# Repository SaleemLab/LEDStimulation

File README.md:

# Full-Field LED Visual Stimulator

An open-source, high-precision visual stimulation platform designed for visual neuroscience, sensory physiology, and human psychophysics. The system delivers temporally agile, multi-chromatic optical stimulation (e.g., Green for M-cones/rods and UV for S-cones, or custom multi-spectral arrays) with sub-millisecond precision.

https://github.com/user-attachments/assets/08af2269-a270-4899-ae75-62786a714254

*Example stimulus: 2 Hz antiphase (Green / UV) sinusoidal flicker.*

---

## Key Capabilities

- **High-Resolution Temporal Modulation:** 16-bit Phase-Correct carrier PWM (~7.68–10 kHz) combined with hardware-interrupt pacing (Timer3 CTC ISR) eliminates visible digital stepping and software loop jitter.
- **Rich Stimulus Battery:** Native microsecond-timed generation of sinusoidal flickers, Gaussian white noise (with Central Limit Theorem PRNG), contrast-switching adaptation sequences, exponential frequency chirps, and stepped luminance pulses.
- **Quantitative Radiometric Calibration:** End-to-end MATLAB calibration pipeline mapping raw duty cycles to linearized lookup tables (LUTs) and calculating exact photoreceptor isomerisation rates ($R^*/\text{photoreceptor/s}$).
- **Flexible Form Factors:** Supports both 200mm full-field panel enclosures (with magnetic diffusion clamping) and miniature wearable mounts for Pupil Labs Neon eye-tracking glasses.
- **Reactive Experiment Orchestration:** Full integration with [Bonsai](https://bonsai-rx.org/) for closed-loop, state-dependent, adaptive psychometric staircase, and LabStreamingLayer (LSL) multi-modal recording.

---

## System Architecture

```mermaid
graph LR
    subgraph Host Software
        Bonsai[Bonsai Reactive Workflows]
        LSL[LabStreamingLayer / LabRecorder]
        MATLAB[MATLAB Calibration Suite]
    end

    subgraph Microcontroller Firmware
        MCU[Arduino Leonardo / Teensy 4.1]
        T1[Timer1: 16-bit PWM]
        T3[Timer3: CTC Interrupt Pacing]
        LUT[PROGMEM Gamma LUT]
    end

    subgraph Hardware & Optics
        Driver[Multi-Channel Driver Stage]
        LEDs[Dual-Channel LED Arrays]
        Enclosure[Magnetic Diffusion Enclosure / Glasses]
        Sensors[Photodiode / Power Meter / Eye Tracker]
    end

    Bonsai -- Serial ASCII (115200) --> MCU
    MATLAB -. Offline Calibration .-> LUT
    MCU --> T1 & T3
    T3 --> LUT --> T1
    T1 --> Driver --> LEDs --> Enclosure
    Enclosure -. Optical Feedback .-> Sensors
    Sensors --> LSL
```

---

## Quickstart Guide

### 1. Flash the Firmware
1. Open [`ArduinoCode/StimulusControlViaSerial_Leonardo_v8/StimulusControlViaSerial_Leonardo_v8.ino`](file:///d:/Code/LEDStimulation/ArduinoCode/StimulusControlViaSerial_Leonardo_v8/StimulusControlViaSerial_Leonardo_v8.ino) in the Arduino IDE.
2. Select **Arduino Leonardo** as your board and choose the corresponding COM port.
3. Click **Upload**.

### 2. Connect Hardware & Verify
1. Connect your LED driver to the designated MCU pins (PWM: Pins 9 & 10; Indicators: Pins 4 & 5).
2. Open the Serial Monitor at `115200` baud.
3. Send a test sinusoidal flicker:
   ```text
   s, 3000, 2.0, 0.0, 0.5, 0.8, 0.8
   ```
   *(Runs a 3-second, 2 Hz antiphase flicker on Channels A and B at 80% contrast).*

### 3. Launch Experimental Workflows
Open [Bonsai](https://bonsai-rx.org/) and load one of the pre-built visual stimulation workflows from [`BonsaiCode/`](file:///d:/Code/LEDStimulation/BonsaiCode/) (e.g., `LEDstimulation_normal.bonsai` or `ManualMethodOfAdjustment.bonsai`).

---

## Documentation Index

Comprehensive guides, schematics, and technical specifications are available in the **[`docs/`](docs/index.md)** directory:

| Section | Description |
| :--- | :--- |
| **[1. Hardware](docs/1-hardware/circuit-and-driver.md)** | [Circuit & Driver](docs/1-hardware/circuit-and-driver.md) • [Custom PCBs](docs/1-hardware/custom-pcbs.md) • [Panel Enclosure](docs/1-hardware/enclosure-and-optics/panel-enclosure.md) • [Wearable Glasses](docs/1-hardware/enclosure-and-optics/wearable-glasses.md) • [Bill of Materials](docs/1-hardware/bill-of-materials.md) |
| **[2. Firmware](docs/2-firmware/architecture-and-timers.md)** | [Architecture & Hardware Timers](docs/2-firmware/architecture-and-timers.md) • [Serial API Reference](docs/2-firmware/serial-api-reference.md) • [Firmware Variants](docs/2-firmware/firmware-variants.md) |
| **[3. Calibration](docs/3-calibration/calibration-guide.md)** | [Calibration Guide](docs/3-calibration/calibration-guide.md) • [Gamma LUT Pipeline](docs/3-calibration/gamma-lut-pipeline.md) • [Photoreceptor Calculations](docs/3-calibration/photoreceptor-calculations.md) |
| **[4. Experimental Workflows](docs/4-experimental-workflows/bonsai-overview.md)** | [Bonsai Setup](docs/4-experimental-workflows/bonsai-overview.md) • [Stimulation Paradigms](docs/4-experimental-workflows/stimulation-paradigms.md) • [Integration & Multi-Modal Sync](docs/4-experimental-workflows/integration-and-sync.md) |
| **[5. Reference](docs/5-reference/performance-and-sync.md)** | [Performance Characteristics, Switching Dynamics & Thermal Notes](docs/5-reference/performance-and-sync.md) |

---

## Repository Structure

```text
├── ArduinoCode/                  # Microcontroller firmware (Leonardo v8, DDS, Teensy 4.1, IMU)
├── BonsaiCode/                   # Main Bonsai visual reactive workflows & stimulus CSVs
├── BonsaiForHumanExperiments/    # Dedicated human psychophysics Bonsai workflows
├── Calibration/                  # MATLAB scripts for radiometry, gamma LUTs & opsin calculations
├── Hardware/                     # CAD files (.stp, .stl, .ipt), KiCad PCB designs & driver schematics
│   ├── Enclosure/                # Baseplate CAD & 3D printed magnetic diffusion clamps
│   ├── glasses/                  # Pupil Labs Neon glasses boom arm & miniature diffuser
│   ├── LED_board/                # KiCad dual-channel LED array PCB
│   └── LED_board_humans/         # KiCad 3-colour LED array PCB (WIP redesign with layout improvements)
├── HumanExpAnalysis/             # MATLAB scripts for IMU movement and behavioural analysis
├── LabRecorderFiles/             # Multi-modal LabStreamingLayer (LSL) recording configurations
└── docs/                         # Modular technical documentation
```

---

## License & Attribution

Developed for scientific research applications. If you use this platform in your research, please cite this repository.

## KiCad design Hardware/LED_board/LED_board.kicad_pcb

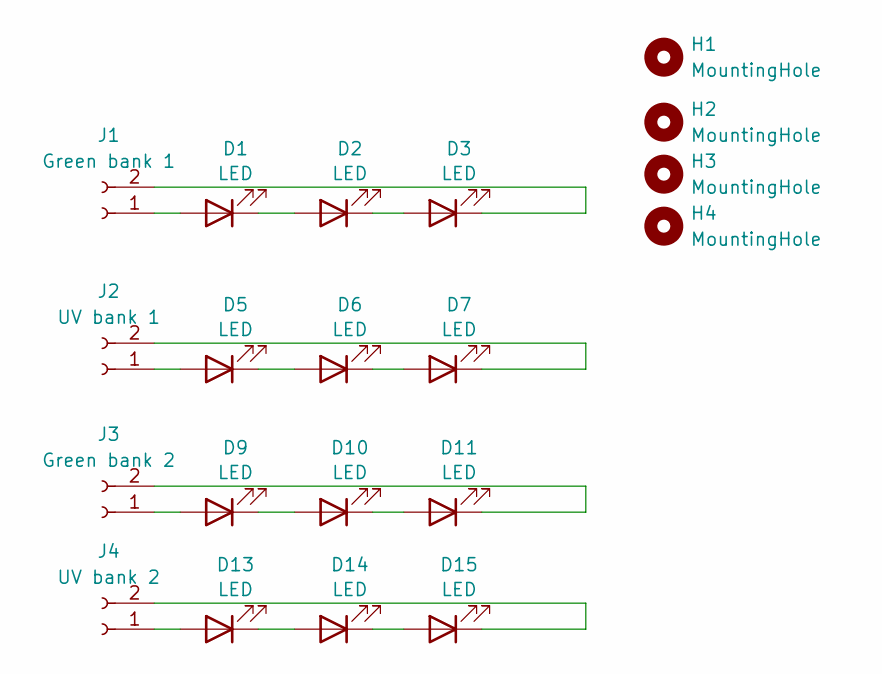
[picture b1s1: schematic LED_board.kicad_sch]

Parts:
D1, D2, D3, D9, D10, D11: LED; LED-SMD_L3.5-W2.8_RED
D5, D6, D7, D13, D14, D15: LED; LED-SMD_L3.5-W2.8-FD_WHITE-1
H1, H2, H3, H4: MountingHole; MountingHole_3.2mm_M3
J1: Green bank 1; PinSocket_1x02_P2.54mm_Horizontal
J2: UV bank 1; PinSocket_1x02_P2.54mm_Horizontal
J3: Green bank 2; PinSocket_1x02_P2.54mm_Horizontal
J4: UV bank 2; PinSocket_1x02_P2.54mm_Horizontal

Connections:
unnamed: D1.2 (A), J1.1
unnamed: D1.1 (K), D2.2 (A)
unnamed: D2.1 (K), D3.2 (A)
unnamed: D3.1 (K), J1.2
unnamed: D5.2 (A), J2.1
unnamed: D5.1 (K), D6.2 (A)
unnamed: D6.1 (K), D7.2 (A)
unnamed: D7.1 (K), J2.2
unnamed: D9.2 (A), J3.1
unnamed: D9.1 (K), D10.2 (A)
unnamed: D10.1 (K), D11.2 (A)
unnamed: D11.1 (K), J3.2
unnamed: D13.2 (A), J4.1
unnamed: D13.1 (K), D14.2 (A)
unnamed: D14.1 (K), D15.2 (A)
unnamed: D15.1 (K), J4.2

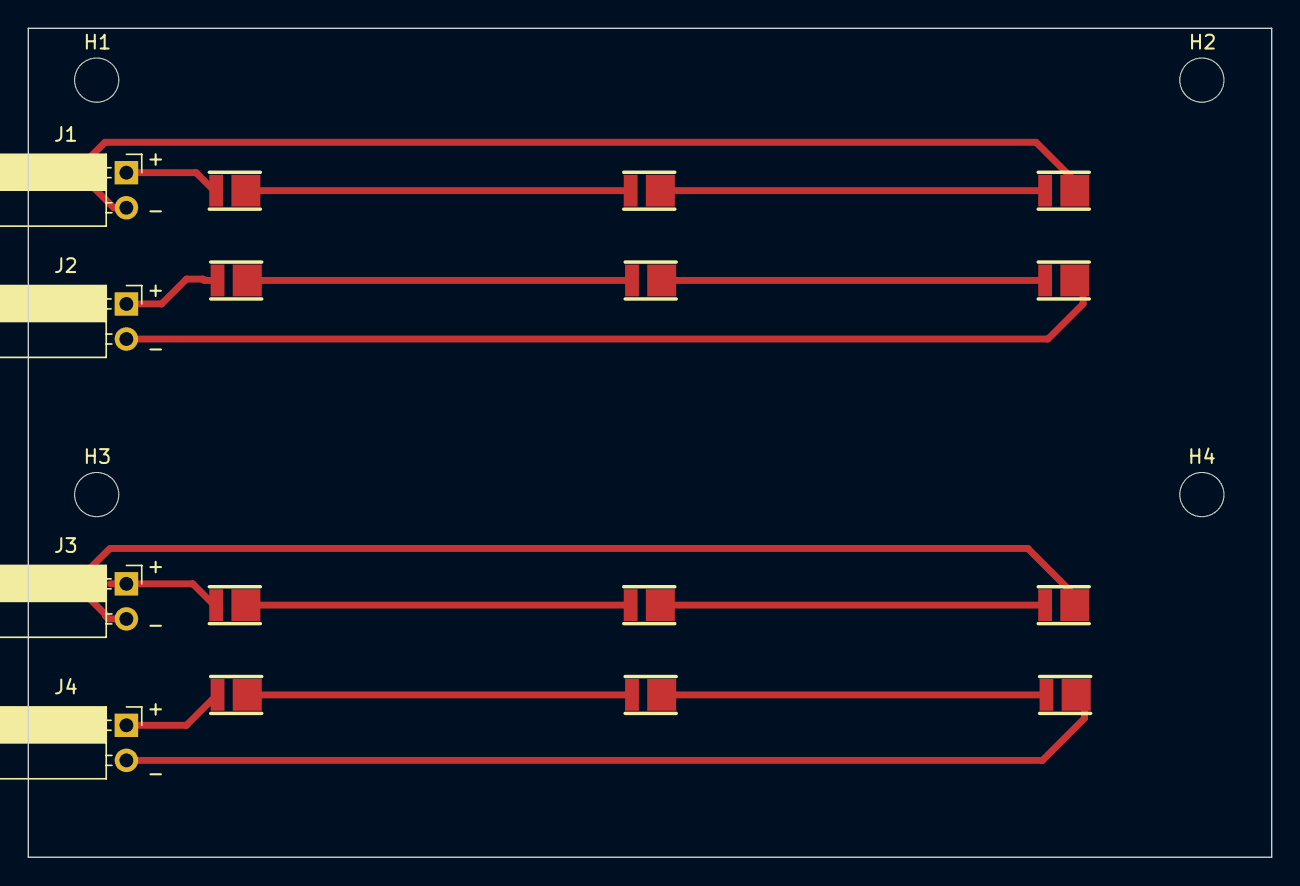
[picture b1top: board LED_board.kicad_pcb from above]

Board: 2 copper layers, 90.0 x 60.0 mm, 20 parts (0 on the bottom side), 16 nets.

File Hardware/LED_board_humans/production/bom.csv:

Designator,Footprint,Quantity,Value,LCSC Part #
"D1, D10, D11, D2, D3, D9",LED-SMD_L3.5-W2.8_RED,6,LED,C2843870
"D13, D14, D15, D5, D6, D7",LED-SMD_L3.5-W2.8-FD_WHITE-1,6,LED,C2843877
"H1, H2, H3, H4",MountingHole_3.2mm_M3,4,MountingHole,
J1,PinSocket_1x02_P2.54mm_Horizontal,1,Green bank 1,
J2,PinSocket_1x02_P2.54mm_Horizontal,1,UV bank 1,
J3,PinSocket_1x02_P2.54mm_Horizontal,1,Green bank 2,
J4,PinSocket_1x02_P2.54mm_Horizontal,1,UV bank 2,

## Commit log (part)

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2024-12-03 porting from MatrixRigs repo
2024-12-05 fixed flicker stimulation workflow
    loading next stimulus + csv
2024-12-05 Sinewave with contrat envelope workflow
2024-12-12 Update StimulusControlViaSerial_Leonardo_v2.ino
    removed 5s 0 lumiannce delay from white noise, this can be set manually now
2024-12-19 changed pin 4 toggle as temp fix for table_index not always going to 0
2024-12-19 made sinewave table index vars global volatile to ensure they are set to 0 before each stimulation routine
2025-01-27 basic flicker analysis update
2025-02-07 fixed sinewave interrupts so that the table_index always starts at 0
2025-02-13 Update StimulusControlViaSerial_Leonardo_v2.ino
    added gamma correction stimulus routine
2025-02-17 calibration workflow for stimulator
2025-02-19 update to calibrations
2025-02-21 wip gamma correction
2025-02-22 pre progmem update
2025-02-24 working on gamma correction
2025-02-24 green120mA gc lut
2025-02-25 Update StimulusControlViaSerial_Leonardo_v3.ino
    added void setOCR1A() which applies requested value using selected gamma lut
2025-02-26 setup workflows for sussex
2025-02-27 WIP on contrast envelope modulation
2025-02-28 two channels for PWM
2025-02-28 2-channel PWM signal
    Split green and UV to diff PWM channels (9 and 10), both on Timer1.
    Bool flags set over serial controls whether each channel is to be set on/off at any time
2025-03-04 Update StimulusControlViaSerial_Leonardo_v4.ino
    added function to check pot values during calibrationa
2025-03-10 wheel speed calc on arduino
2025-03-25 basic sine flicker workflow working again (UCL version)
2025-03-25 removed print from arduino code
2025-04-12 reorganise dirs
2025-04-12 Update README.md
    Vref circuit description
2025-04-15 added some hardware
2025-04-16 update hardware
2025-04-29 gaussian white noise sequences
2025-05-01 Update StimulusControlViaSerial_Leonardo_v5.ino
    Refactoring and clean-up of arudino stimulus code
2025-05-01 gaussian white noise update
    Updated code for white noise stimuli.
    1) now uses gaussian white noise, where random values are approx. gaussian using CLT
    2) fractional mean and std of TopLumi are additional input args
    3) if useChA and useChB, independent gaussian white noise sequences will be used
2025-05-01 Update StimulusControlViaSerial_Leonardo_v5.ino
    Added phase offset (ChB relative to ChA) parameter for sinewave stimulation
2025-05-02 Update StimulusControlViaSerial_Leonardo_v5.ino
    "useChA/B" now means that current ocr values wont be updated during main stimulus functions, but can still be set by setDutyCycle.
    No longer defaults to turning off led either, but maintains current value.
2025-05-09 Updated sine wave stimuation
    can now choose
    phase and contrast for chA and chB independently
2025-05-09 Set duty cycles for set durations
    "sdt" function that can set duty cycles of channels for specific periods before returning to mean luminance
2025-05-16 Ported matrix rigs local bonsai and basic workflow
2025-05-19 moving old arduino files to archive
2025-05-19 updated frozenWhiteNoise and SwitchingWhiteNoise
2025-05-19 added flicker sweep functionality
2025-05-20 Revert "reorganise dirs"
    This reverts commit e67b3b7d989c3398e2d401127244eebda8839525.
2025-05-20 Revert "added flicker sweep functionality"
    This reverts commit 4845784872e3e7352c07020bf213f54e47fcadcb.
2025-05-20 fixing broke
2025-05-20 clean
2025-05-20 clean up pt2
2025-05-20 re-up
2025-05-20 Create StimulusControlViaSerial_Leonardo_v7.ino
    frequency sweep and frozen white noise stim
2025-05-21 calibration of new setup init
2025-05-21 updating indicator pin behaviour (see issues)
2025-05-21 some indicator pin updates and new bonsai workflow specification style
2025-05-21 non-state-dependent workflow
2025-05-21 added channel selection from bonsai workflows functionality
    e.g. for frozen white noise
2025-05-22 updating calibration code to work with PDA100A2 pd
2025-05-22 Update ganzfeldCalibration_v5.m
    tiny plot axis update
2025-05-22 Gamma correction
    including to dynamically select the required LUT
2025-05-23 corrected types in arduino code
2025-05-28 updates pre first recording
2025-05-30 spec files for chromatic stim
2025-05-30 some stimulus spec files and updating white noise generaiton
2025-06-02 updating gaussian CLT random number generation
2025-06-02 testing new white noise generation + added timestamp to arduino PWM data in bonsai
2025-06-03 organise stimulus spec csv files
2025-06-03 replaced serial.println withn Serial.print("\n")
2025-06-03 nice formatting of arduinoPWM csv logging
2025-06-09 high rep sinewaves spec file
2025-06-12 WhiteNoise STA analysis update
2025-06-18 Update StimulusControlViaSerial_Leonardo_v8.ino
    automatic gamma correction application based on potentiometer settings
2025-06-18 reorgansie stimulus spec files
2025-07-02 pre clean up of preprocessing
2025-07-07 Refactor STA analysis and add modular helpers
    Replaces in-line stimulus processing in WN_STA_analysis.m with a call to a new processStimulusData function for improved modularity and memory efficiency. Adds calculateSTA and calculateSTC helper fu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
2025-07-10 update white noise analysis
2025-08-15 Remove unused Bonsai workflow files
    Deleted multiple Bonsai workflow and layout files related to FlickerStimulation, Ganzfeld, and LEDstimulation workflows. This cleanup removes obsolete or unused experiment configurations from the rep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
2025-10-15 updated hardcoded com ports
2025-10-16 analysis
2025-10-18 Refactor flicker trial extraction and alignment pipeline
    Rewrote getFlickerTrialInfo_dev.m to use a modular, block-based approach for extracting and aligning flicker trials, with improved wheel data alignment and trial property injection. Updated crateTria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
2025-11-14 update driver circuit info
    Removed detailed sections on LED stimulation and driver design from the README.
2025-11-14 Update LED section with new links
    Replaced custom LED PCB link with links to green and UV LEDs.
2025-12-18 Enhance README with command descriptions and new features
    Updated descriptions for stimulus commands and configuration commands in README.md. Added new command for timed luminance step and clarified existing commands.
2025-12-18 Change 'Time' to 'Duration' in README
    Updated parameter name from 'Time' to 'Duration' in timed luminance step.
2025-12-18 Update README with Timer configuration details
    Added future plans for Timer3 and Timer4 configuration.
2025-12-18 Add Performance Characteristics section to README
    Added a new section on Performance Characteristics detailing switching dynamics, linearity, resolution, and thermal stability.
2026-01-04 added example video
2026-01-04 Update README with example stimulus details
    Added example stimulus information to README.
2026-01-04 Update README with example stimulus description
2026-01-04 removed analysis
2026-01-24 Revise 'Performance Characteristics' section in README
2026-03-17 eeg arduino code wip. stepped flicker sweep
2026-03-17 Add per-channel contrast to sine envelope
    chA/B max contrast options for contrast envelope
2026-03-18 added basic workflow for just running stimuli
2026-03-18 updated stim only workflow
2026-03-18 started working on task logic
    click sounds for stim on/off
2026-03-25 added audio clicks
2026-04-02 pre-fix envelope freq issue
2026-04-02 fixed contrast envelpe frequency
2026-04-02 added test panel gamma correction
2026-04-02 gamma retest
2026-04-02 bench supply gc try
2026-04-02 raised cosine contrast envelope
2026-04-02 exploring DDS approach for sinewaves
2026-04-02 some bug fixes for DDS code
2026-04-02 2-freqyuency control
2026-04-02 removed some unused code
2026-04-09 fixed buggy lut on 8bit DDS code
2026-04-14 initial port of stimuation software to Teensy
2026-04-22 updating arduino code
2026-04-22 wip - improving code performance
2026-04-22 Optimize LUTs, types, and ISR performance
    Convert 8-bit lookup tables and related pointers to PROGMEM uint8_t to save memory and simplify reads; update pgm_read_* calls accordingly. Replace 32-bit math with 16-/8-bit operations where safe (t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
2026-04-22 Optimize ISR math and reduce LUT size
    Reduce memory and speed up interrupt code: change raisedCosineLUT to uint8_t and scale it 0–255, change contrast scaling from 256->255 across functions, and add a 32-bit fadePhase accumulator to repl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
2026-04-22 perfect frequencies
    Replace expensive 64-bit division in calcPhaseInc with a precomputed float multiplier (137438.953125f) for a faster exact result. Refactor ISR code to use 16-bit arithmetic where safe: cast operands 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
2026-05-06 manualMethodsOfAdjustent bonsaicode
2026-05-06 l/r button press arduino
2026-05-07 Add delays and expand Bonsai staircase workflow
    Arduino: insert 2000µs delayMicroseconds() at end of several stimulus routines (outputSinewave, SineContrastConv, SteppedFrequencySweep, FrequencySweep, setDutyCycleTime, cycleDutyCycles) so USB has 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
    Bonsai: significantly extend staircase_dev.bonsai by replacing the simple key input with a full staircase workflow (CreateDiscreteUniform, StaircaseProcedure, WithLatestFrom/Zip, Conditions, Behavior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
2026-05-07 added catch in bonsai workflow in case stimulus end marker is not received from arudino
2026-05-07 organised staircase workflow
2026-05-07 update staircase workflow to work with sine flicker and sinewave envelope
2026-05-07 added modifiable step size to staircase workflow
2026-05-07 added click audio and logging to staircase
2026-05-12 added "reversal frequencies" visualiser
2026-05-13 aman testing stim
2026-05-13 Created human experiment specific bonsai folder
2026-05-13 Added mean reversal frequency tracking
2026-05-13 Added multiple step sizes functionality
2026-05-13 added YesNo response and click
    Temp click sound as have no idea how to properly control audio playback
2026-05-13 figured out audio playback
2026-05-14 implemented double click for yes/no and cleaner visualizer window
2026-05-14 fixing werid directory issues
2026-05-14 Started work on general task workflow
2026-05-14 Update GeneralTaskWorkflow
2026-05-14 update general task workflow
2026-05-14 working on general workflow
2026-05-15 improved pausing functionality
2026-05-15 added Method of constant stimuli
2026-05-15 Added clicks and ISI
2026-05-15 filename saving
2026-05-15 dynamics step sizes for staircases
2026-05-15 Added performance visualisers
2026-05-18 Updated visualisers
    nTrial counting, currentTrial values
2026-05-18 Externalised trial manager properties
2026-05-18 externalise visualisers
2026-05-18 eternalised main stimuli parameters
2026-05-28 imu testing
2026-05-28 pilot eeg workflows
2026-05-28 flicker sweep EEG pilot workflow
2026-05-28 fixed click timing for freq sweep workflow
2026-06-04 eeg pilot workflows
2026-06-04 imu dev
2026-06-04 gitignore
2026-06-04 imu tracking data csv
2026-06-10 2-interval response for discrim and yes/no
2026-06-10 integrated IMU into task workflow
2026-06-16 Tided up arduino code dir and added new mouse rig dds
2026-06-16 stepped freq sweep stimulus for mouse rig
2026-06-16 added pupil labs 3d printing files
2026-06-16 reorganise glasses 3d printing files
2026-06-17 fix clicks hotfix
2026-06-25 local changes up (no big changes)
2026-06-25 added balanced left/right trial blocks
2026-06-25 added state alternation logic
2026-06-29 LSL test
